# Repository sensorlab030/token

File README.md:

Small PCB to be used by the Sensor Lab events.

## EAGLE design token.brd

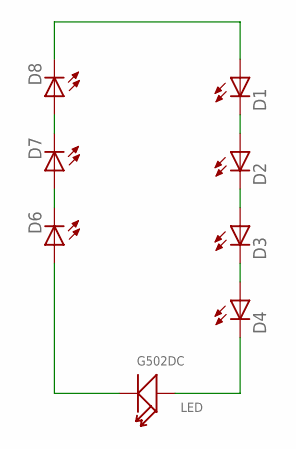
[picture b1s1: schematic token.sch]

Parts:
D1, D2, D3, D4, D6, D7, D8: LEDSQR2X5; LED2X5
LED: G502DC; LED2-2.54-D5.0MM

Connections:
unnamed: D1.A, D8.K (C)
unnamed: D1.K (C), D2.A
unnamed: D2.K (C), D3.A
unnamed: D3.K (C), D4.A
unnamed: D4.K (C), LED.+
unnamed: D6.A, LED.-
unnamed: D6.K (C), D7.A
unnamed: D7.K (C), D8.A

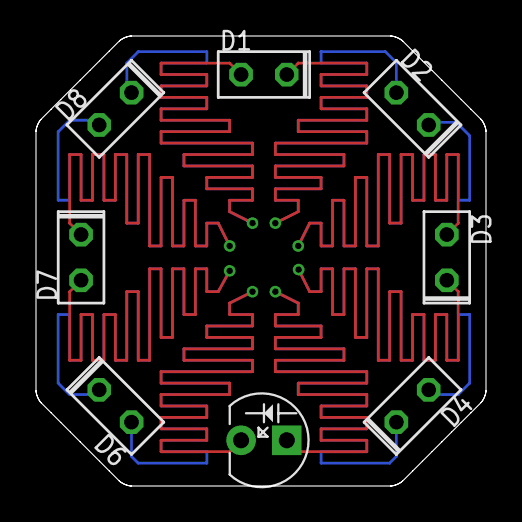
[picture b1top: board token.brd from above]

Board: 2 copper layers, 25.0 x 25.0 mm, 8 parts (0 on the bottom side), 8 nets.

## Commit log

2017-10-09 Added attribution to readme
2017-10-11 Added hexagon outline
2017-10-11 Added logo silks
2017-10-11 Rearranged parts, updated routing
2017-10-11 Added PCB art
2017-10-13 Initial wiring and routing
2017-10-25 Final adjustments before CAM
2017-10-25 Added CAM file
